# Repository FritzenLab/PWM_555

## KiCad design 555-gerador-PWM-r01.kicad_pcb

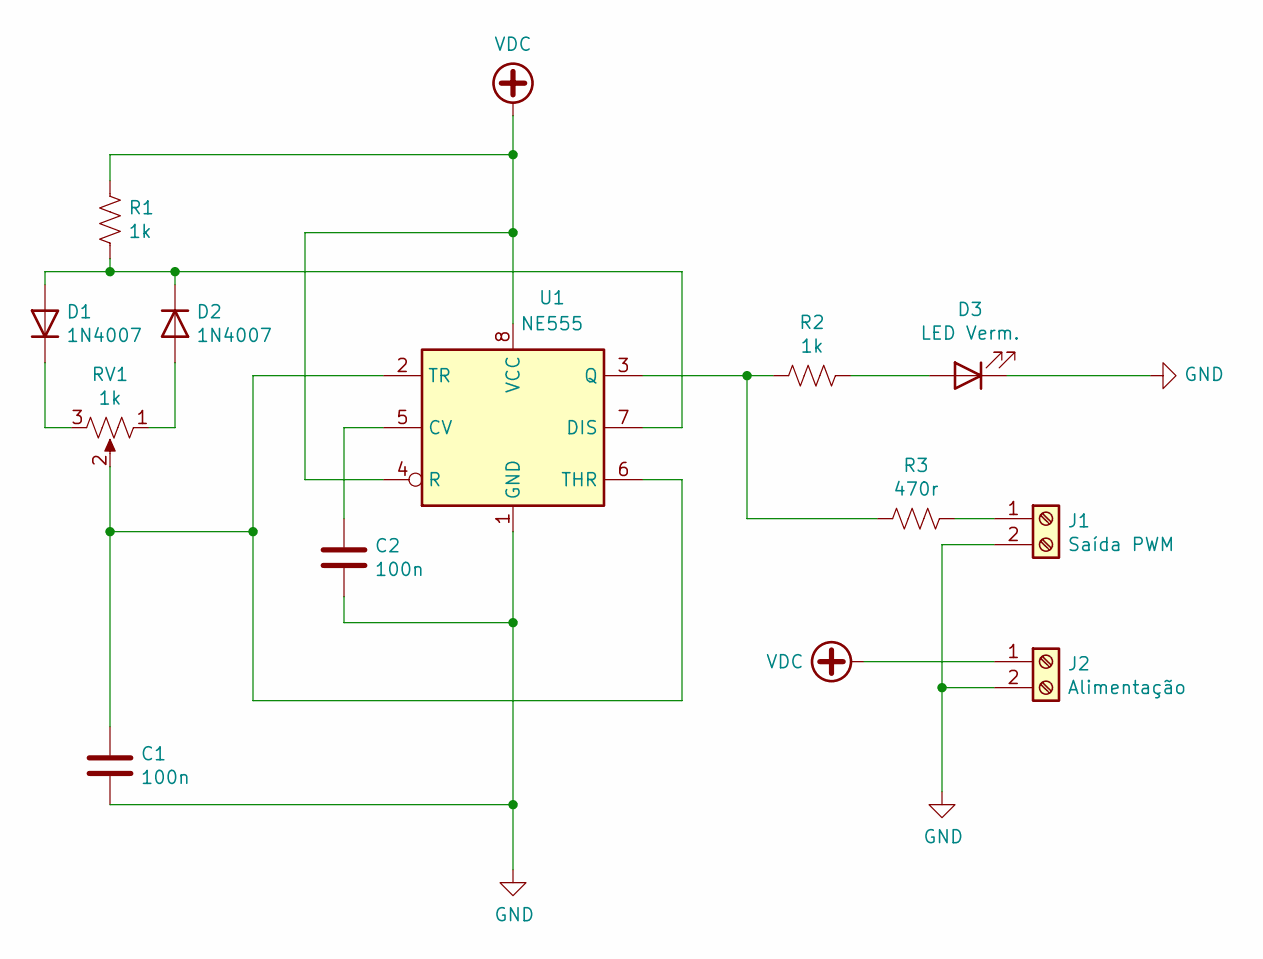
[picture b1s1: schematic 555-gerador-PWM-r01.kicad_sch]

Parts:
C1, C2: 100n; C_Disc_D3.0mm_W2.0mm_P2.50mm
D1, D2: 1N4007; D_DO-41_SOD81_P10.16mm_Horizontal
D3: LED Verm.; LED_D5.0mm_Clear
J1: Saída PWM; PhoenixContact_MCV_1,5_2-G-5.08_1x02_P5.08mm_Vertical
J2: Alimentação; PhoenixContact_MCV_1,5_2-G-5.08_1x02_P5.08mm_Vertical
R1, R2: 1k; R_Axial_DIN0207_L6.3mm_D2.5mm_P10.16mm_Horizontal
R3: 470r; R_Axial_DIN0207_L6.3mm_D2.5mm_P10.16mm_Horizontal
RV1: 1k; Potentiometer_Alps_RK163_Single_Horizontal
U1: NE555; DIP-8_W7.62mm_Socket_LongPads

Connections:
GND: C1.2, C2.2, D3.1 (K), J1.2, J2.2, U1.1 (GND)
unnamed: C1.1, RV1.2, U1.2 (TR), U1.6 (THR)
unnamed: C2.1, U1.5 (CV)
unnamed: D1.1 (K), RV1.3
unnamed: D1.2 (A), D2.1 (K), R1.2, U1.7 (DIS)
unnamed: D2.2 (A), RV1.1
unnamed: D3.2 (A), R2.1
unnamed: J1.1, R3.1
unnamed: R2.2, R3.2, U1.3 (Q)
VDC: J2.1, R1.1, U1.4 (R), U1.8 (VCC)

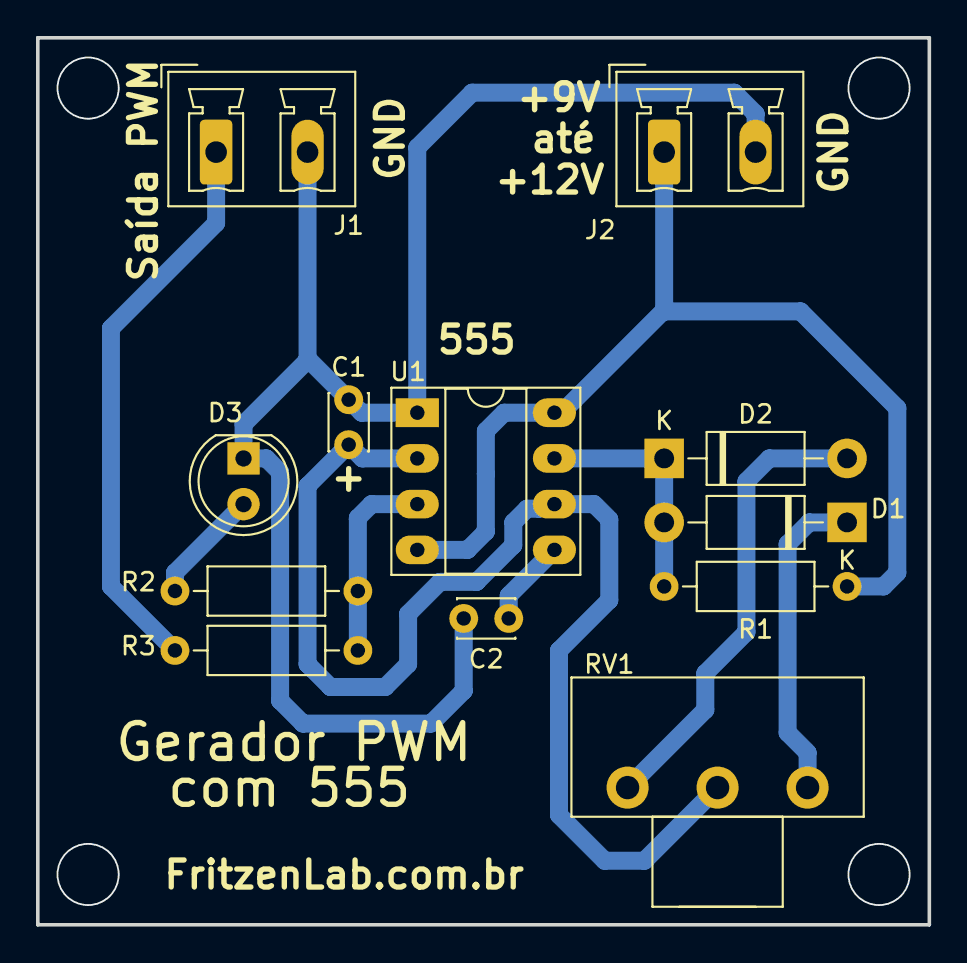
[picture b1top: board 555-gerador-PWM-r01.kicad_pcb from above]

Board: 2 copper layers, 49.5 x 49.3 mm, 12 parts (0 on the bottom side), 10 nets.

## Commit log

2019-02-10 primeira revisao
2019-02-10 adicionado leia-me
    adicionado arquivo leia-me
2019-02-10 revisados furos (removido GND)
2024-11-03 generated gerbers R02
2024-11-03 added images
2024-11-03 backups
